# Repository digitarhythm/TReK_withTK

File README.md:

# TReK withTK
Macropad TenKey pad with RP2040-Zero.

[Firmware repository](https://github.com/digitarhythm/qmk_firmware/tree/digitarhythm/keyboards/trek/withtk)

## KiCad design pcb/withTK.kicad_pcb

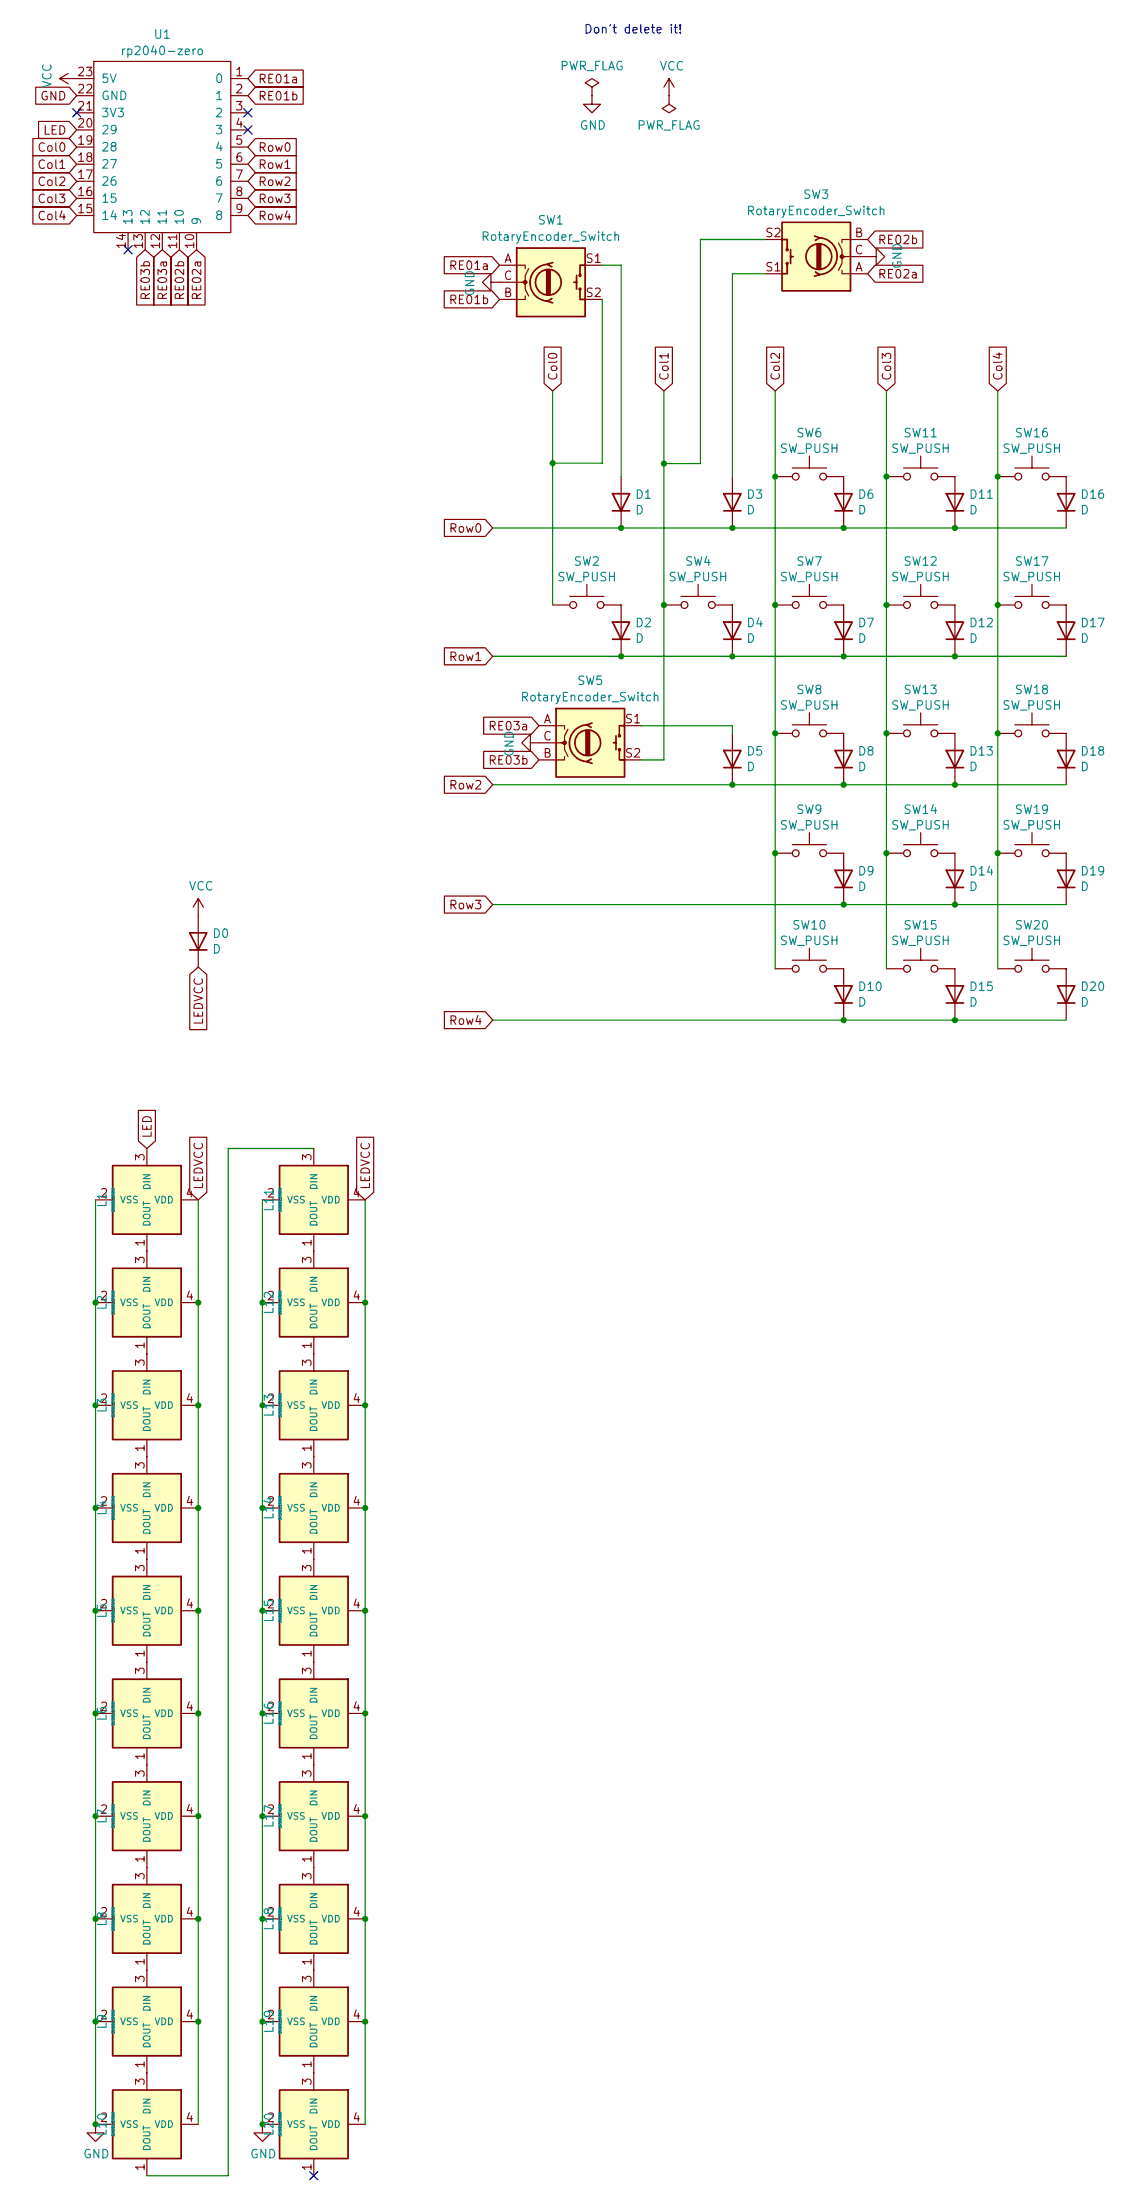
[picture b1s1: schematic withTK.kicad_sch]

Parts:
D0, D1, D2, D3, D4, D5, D6, D7, D8, D9, D10, D11, D12, D13, D14, D15, D16, D17, D18, D19, D20: D; Diode_SMD
L1, L2, L3, L4, L5, L6, L7, L8, L9, L10, L11, L12, L13, L14, L15, L16, L17, L18, L19, L20: SK6812MINI; LED_SK6812MINI-E_BL
SW1, SW3, SW5: RotaryEncoder_Switch; SW_Cherry_MX_1.00u_Kailh_EC12
SW2, SW4, SW6, SW7, SW8, SW9, SW10, SW11, SW12, SW13, SW14, SW15, SW16, SW17, SW18, SW19, SW20: SW_PUSH; CherryMX_Hotswap_1u
U1: rp2040-zero; rp2040-zero-smd-rev-with-th

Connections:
Col0: SW1.S2, SW2.1, U1.19 (28)
Col1: SW3.S2, SW4.1, SW5.S2, U1.18 (27)
Col2: SW6.1, SW7.1, SW8.1, SW9.1, SW10.1, U1.17 (26)
Col3: SW11.1, SW12.1, SW13.1, SW14.1, SW15.1, U1.16 (15)
Col4: SW16.1, SW17.1, SW18.1, SW19.1, SW20.1, U1.15 (14)
GND: L1.2 (VSS), L2.2 (VSS), L3.2 (VSS), L4.2 (VSS), L5.2 (VSS), L6.2 (VSS), L7.2 (VSS), L8.2 (VSS), L9.2 (VSS), L10.2 (VSS), L11.2 (VSS), L12.2 (VSS), L13.2 (VSS), L14.2 (VSS), L15.2 (VSS), L16.2 (VSS), L17.2 (VSS), L18.2 (VSS), L19.2 (VSS), L20.2 (VSS), SW1.C, SW3.C, SW5.C, U1.22 (GND)
LED: L1.3 (DIN), U1.20 (29)
LEDVCC: D0.1 (K), L1.4 (VDD), L2.4 (VDD), L3.4 (VDD), L4.4 (VDD), L5.4 (VDD), L6.4 (VDD), L7.4 (VDD), L8.4 (VDD), L9.4 (VDD), L10.4 (VDD), L11.4 (VDD), L12.4 (VDD), L13.4 (VDD), L14.4 (VDD), L15.4 (VDD), L16.4 (VDD), L17.4 (VDD), L18.4 (VDD), L19.4 (VDD), L20.4 (VDD)
unnamed: D1.2 (A), SW1.S1
unnamed: D2.2 (A), SW2.2
unnamed: D3.2 (A), SW3.S1
unnamed: D4.2 (A), SW4.2
unnamed: D5.2 (A), SW5.S1
unnamed: D6.2 (A), SW6.2
unnamed: D7.2 (A), SW7.2
unnamed: D8.2 (A), SW8.2
unnamed: D9.2 (A), SW9.2
unnamed: D10.2 (A), SW10.2
unnamed: D11.2 (A), SW11.2
unnamed: D12.2 (A), SW12.2
unnamed: D13.2 (A), SW13.2
unnamed: D14.2 (A), SW14.2
unnamed: D15.2 (A), SW15.2
unnamed: D16.2 (A), SW16.2
unnamed: D17.2 (A), SW17.2
unnamed: D18.2 (A), SW18.2
unnamed: D19.2 (A), SW19.2
unnamed: D20.2 (A), SW20.2
unnamed: L1.1 (DOUT), L2.3 (DIN)
unnamed: L2.1 (DOUT), L3.3 (DIN)
unnamed: L3.1 (DOUT), L4.3 (DIN)
unnamed: L4.1 (DOUT), L5.3 (DIN)
unnamed: L5.1 (DOUT), L6.3 (DIN)
unnamed: L6.1 (DOUT), L7.3 (DIN)
unnamed: L7.1 (DOUT), L8.3 (DIN)
unnamed: L8.1 (DOUT), L9.3 (DIN)
unnamed: L9.1 (DOUT), L10.3 (DIN)
unnamed: L10.1 (DOUT), L11.3 (DIN)
unnamed: L11.1 (DOUT), L12.3 (DIN)
unnamed: L12.1 (DOUT), L13.3 (DIN)
unnamed: L13.1 (DOUT), L14.3 (DIN)
unnamed: L14.1 (DOUT), L15.3 (DIN)
unnamed: L15.1 (DOUT), L16.3 (DIN)
unnamed: L16.1 (DOUT), L17.3 (DIN)
unnamed: L17.1 (DOUT), L18.3 (DIN)
unnamed: L18.1 (DOUT), L19.3 (DIN)
unnamed: L19.1 (DOUT), L20.3 (DIN)
RE01a: SW1.A, U1.1 (0)
RE01b: SW1.B, U1.2 (1)
RE02a: SW3.A, U1.10 (9)
RE02b: SW3.B, U1.11 (10)
RE03a: SW5.A, U1.12 (11)
RE03b: SW5.B, U1.13 (12)
Row0: D1.1 (K), D3.1 (K), D6.1 (K), D11.1 (K), D16.1 (K), U1.5 (4)
Row1: D2.1 (K), D4.1 (K), D7.1 (K), D12.1 (K), D17.1 (K), U1.6 (5)
Row2: D5.1 (K), D8.1 (K), D13.1 (K), D18.1 (K), U1.7 (6)
Row3: D9.1 (K), D14.1 (K), D19.1 (K), U1.8 (7)
Row4: D10.1 (K), D15.1 (K), D20.1 (K), U1.9 (8)
VCC: D0.2 (A), U1.23 (5V)

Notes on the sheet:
Don't delete it!

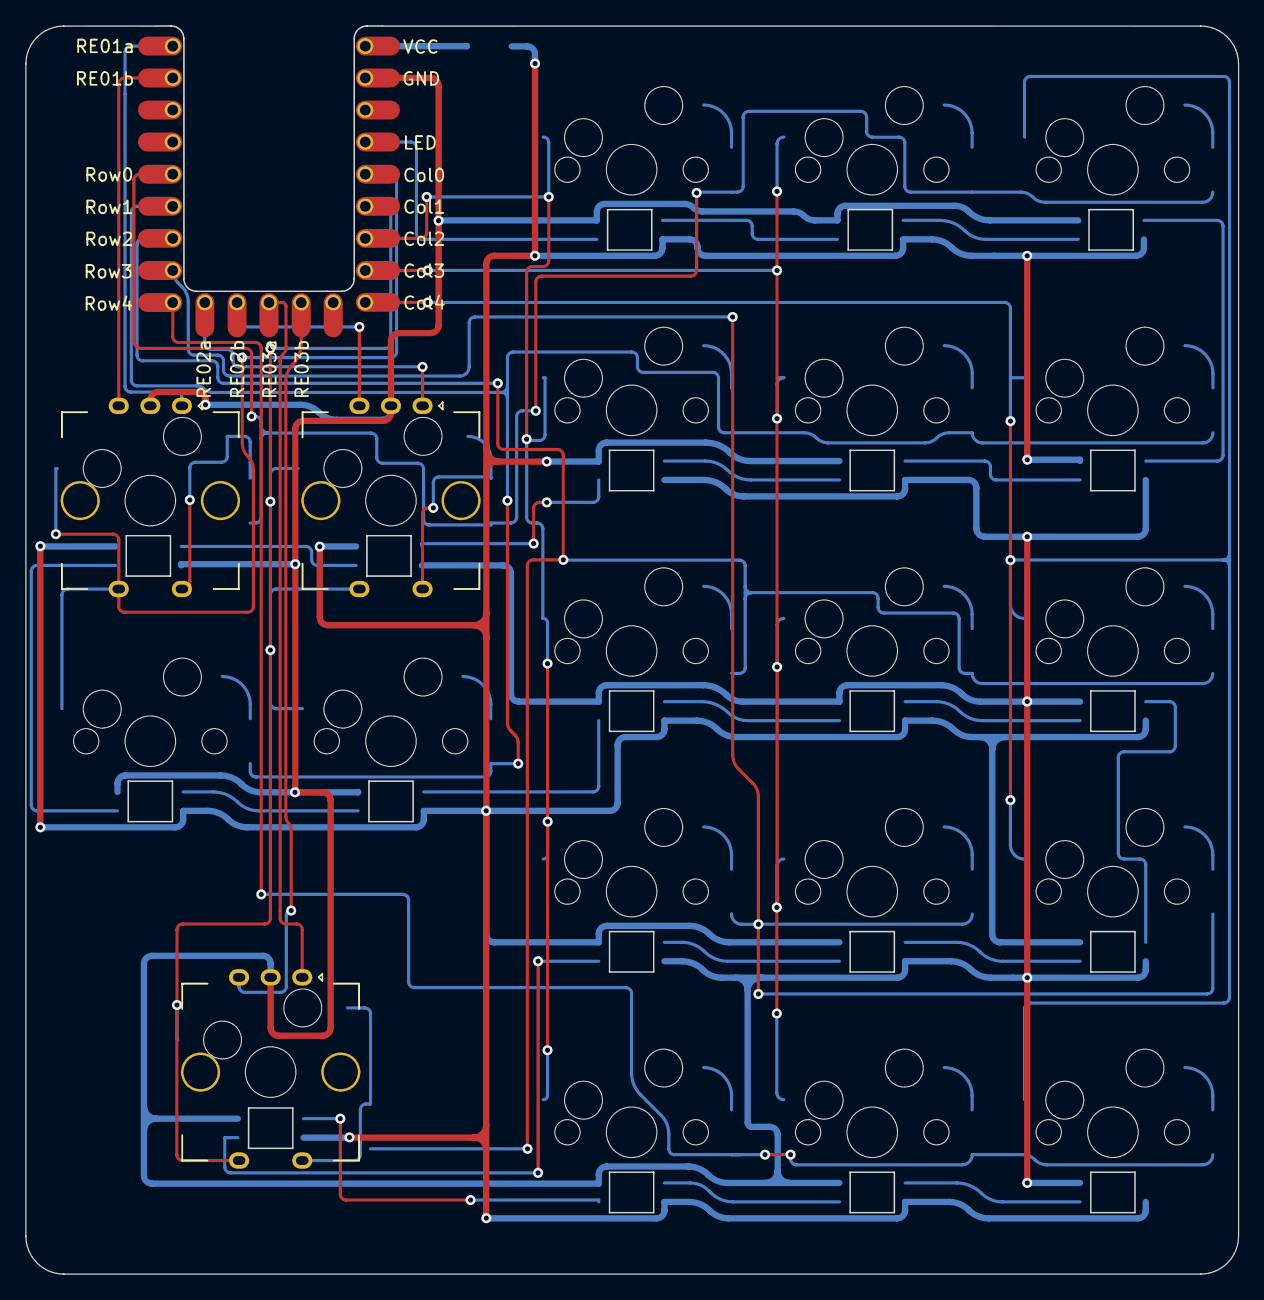
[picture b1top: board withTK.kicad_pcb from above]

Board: 2 copper layers, 96.0 x 98.8 mm, 62 parts (0 on the bottom side), 59 nets.

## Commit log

2024-02-06 Add keyboard firmware.
